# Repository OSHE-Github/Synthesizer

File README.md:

# Synthesizer

**Tips for uploading and running firmware on the Teensy**

- You will need the Arduino IDE to upload the firmware to the Teensy. Instructions: [Arduino IDE install instructions](https://support.arduino.cc/hc/en-us/articles/360019833020-Download-and-install-Arduino-IDE)
- Once Arduino IDE is installed, you will need the Teensyduino support package for Arduino IDE. Instructions: [Teensyduino install instructions](https://www.pjrc.com/teensy/td_download.html)
- You will also need to add the MIDI library into Arduino IDE. Instructions: [MIDI library instrall instructions](https://www.pjrc.com/teensy/td_libs_MIDI.html)
- The firmware should then be able to compile in Arduino IDE and upload to the Teensy by clicking the upload button. Make sure the Teensy is selected by going to Tools/Ports/ and select the correct serial port the Teensy is plugged into.

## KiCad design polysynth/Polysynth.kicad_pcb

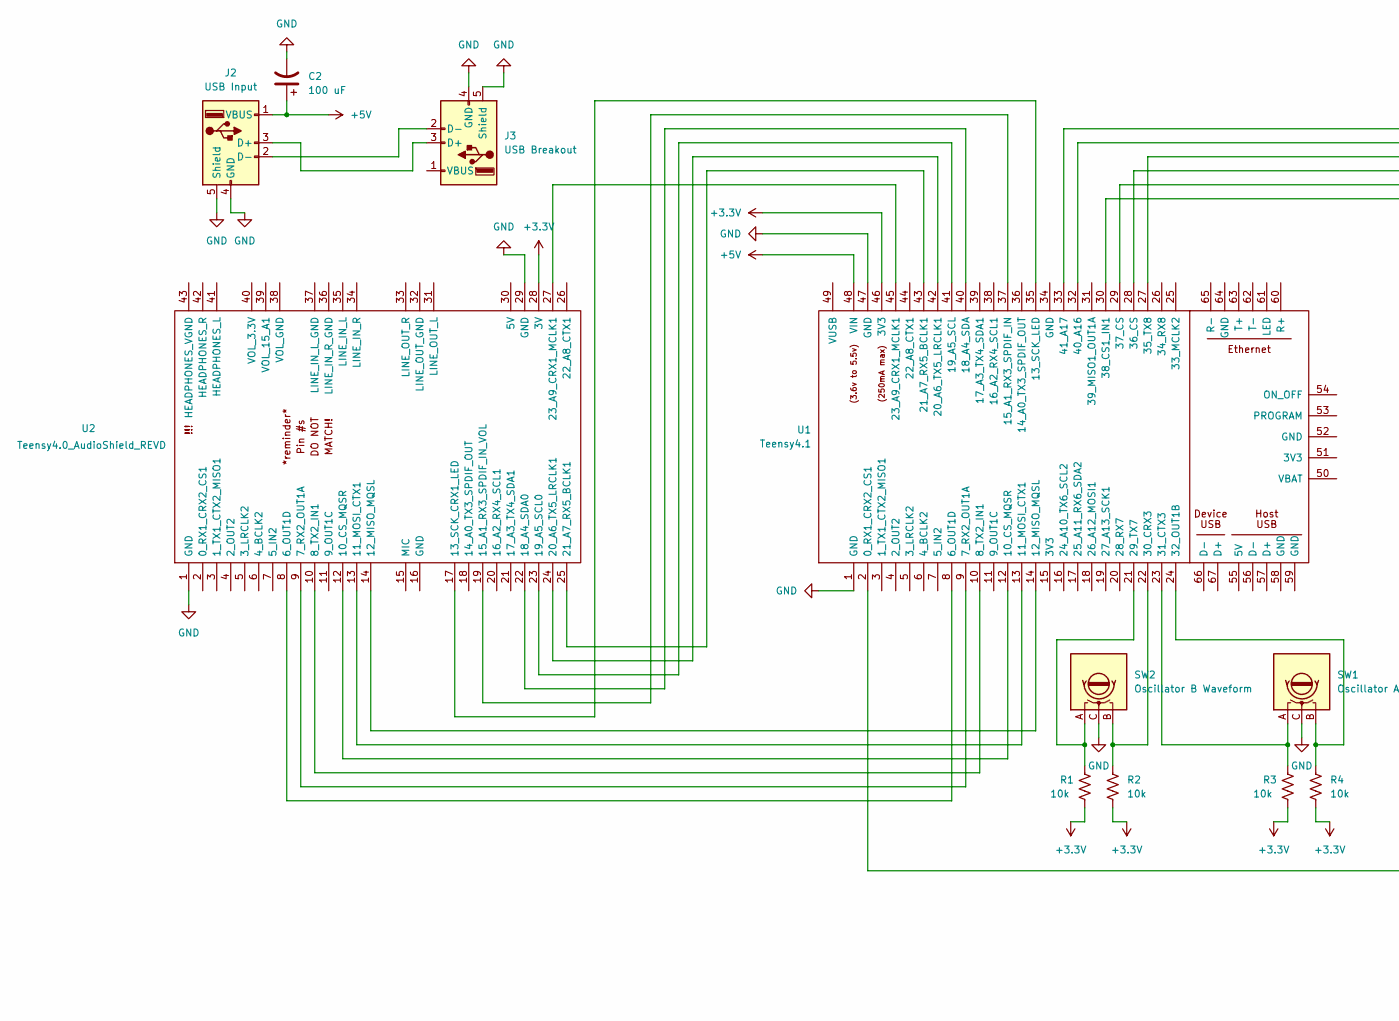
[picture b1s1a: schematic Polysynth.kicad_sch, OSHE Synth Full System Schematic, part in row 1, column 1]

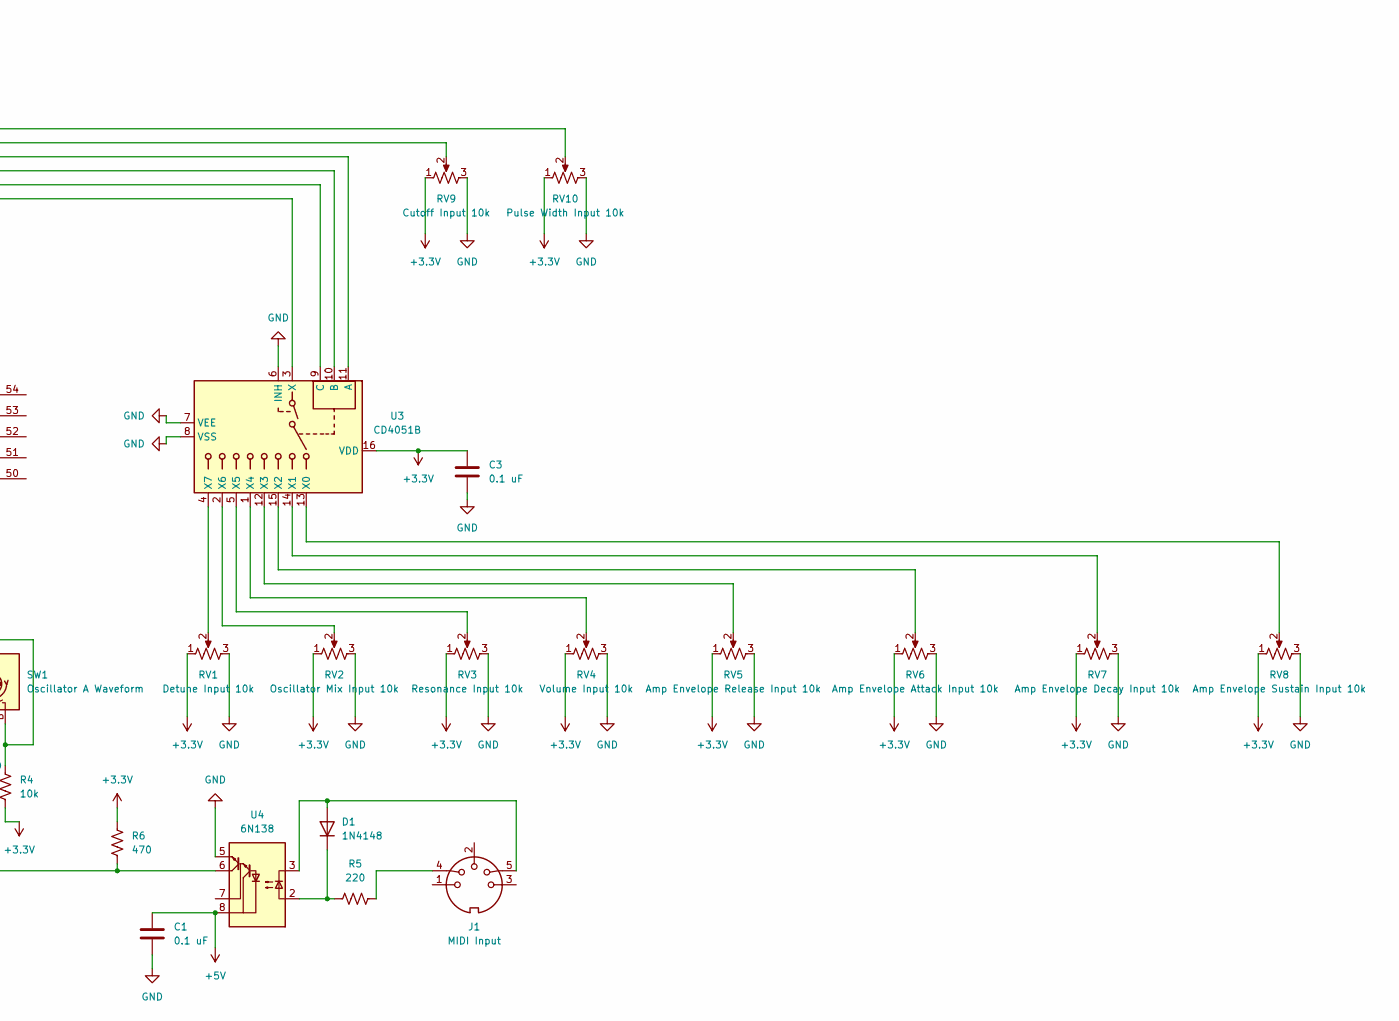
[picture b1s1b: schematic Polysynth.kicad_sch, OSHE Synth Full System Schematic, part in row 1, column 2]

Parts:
C1, C3: 0.1 uF; radial_cap
C2: 100 uF; radial_cap_med
D1: 1N4148; DO-35_02_VIS
J1: MIDI Input; MIDI
J2: USB Input; USB_A_Stewart_SS-52100-001_Horizontal
J3: USB Breakout; USB_A_Stewart_SS-52100-001_Horizontal
R1, R2, R3, R4: 10k; R_Axial_DIN0207_L6.3mm_D2.5mm_P10.16mm_Horizontal
R5: 220; R_Axial_DIN0207_L6.3mm_D2.5mm_P10.16mm_Horizontal
R6: 470; R_Axial_DIN0207_L6.3mm_D2.5mm_P10.16mm_Horizontal
RV1: Detune Input 10k; Potentiometer_Bourns_PTA4543_Single_Slide
RV2: Oscillator Mix Input 10k; PDB12H4301103BF
RV3: Resonance Input 10k; Potentiometer_Bourns_PTA4543_Single_Slide
RV4: Volume Input 10k; Potentiometer_Bourns_PTA4543_Single_Slide
RV5: Amp Envelope Release Input 10k; Potentiometer_Bourns_PTA4543_Single_Slide
RV6: Amp Envelope Attack Input 10k; Potentiometer_Bourns_PTA4543_Single_Slide
RV7: Amp Envelope Decay Input 10k; Potentiometer_Bourns_PTA4543_Single_Slide
RV8: Amp Envelope Sustain Input 10k; Potentiometer_Bourns_PTA4543_Single_Slide
RV9: Cutoff Input 10k; Potentiometer_Bourns_PTA4543_Single_Slide
RV10: Pulse Width Input 10k; Potentiometer_Bourns_PTA4543_Single_Slide
SW1: Oscillator A Waveform; RotaryEncoder_Bourns_Vertical_PEC12R-3x17F-Nxxxx
SW2: Oscillator B Waveform; RotaryEncoder_Bourns_Vertical_PEC12R-3x17F-Nxxxx
U1: Teensy4.1; Teensy41
U2: Teensy4.0_AudioShield_REVD; 4.0audioshield
U3: CD4051B; CD4051BE
U4: 6N138

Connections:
+3.3V: C3.1, R1.2, R2.2, R3.2, R4.2, R6.1, RV1.1, RV2.1, RV3.1, RV4.1, RV5.1, RV6.1, RV7.1, RV8.1, RV9.1, RV10.1, U1.46 (3V3), U2.28 (3V), U3.16 (VDD)
+5V: C1.2, C2.1, J2.1 (VBUS), U1.48 (VIN), U4.8 (VCC)
GND: C1.1, C2.2, C3.2, J2.4 (GND), J2.5 (Shield), J3.4 (GND), J3.5 (Shield), RV1.3, RV2.3, RV3.3, RV4.3, RV5.3, RV6.3, RV7.3, RV8.3, RV9.3, RV10.3, SW1.C, SW2.C, U1.1 (GND), U1.47 (GND), U2.1 (GND), U2.29 (GND), U3.6 (INH), U3.7 (VEE), U3.8 (VSS), U4.5 (GND)
unnamed: D1.2 (A), J1.5, U4.3 (C2)
unnamed: D1.1 (K), R5.1, U4.2 (C1)
unnamed: J1.4, R5.2
unnamed: J2.3 (D+), J3.3 (D+)
unnamed: J2.2 (D-), J3.2 (D-)
unnamed: R6.2, U1.2 (0_RX1_CRX2_CS1), U4.6 (VO2)
unnamed: U1.8 (6_OUT1D), U2.8 (6_OUT1D)
unnamed: U1.9 (7_RX2_OUT1A), U2.9 (7_RX2_OUT1A)
unnamed: U1.10 (8_TX2_IN1), U2.10 (8_TX2_IN1)
unnamed: U1.12 (10_CS_MQSR), U2.12 (10_CS_MQSR)
unnamed: U1.13 (11_MOSI_CTX1), U2.13 (11_MOSI_CTX1)
unnamed: U1.14 (12_MISO_MQSL), U2.14 (12_MISO_MQSL)
unnamed: U1.35 (13_SCK_LED), U2.17 (13_SCK_CRX1_LED)
unnamed: U1.37 (15_A1_RX3_SPDIF_IN), U2.19 (15_A1_RX3_SPDIF_IN_VOL)
unnamed: U1.40 (18_A4_SDA), U2.22 (18_A4_SDA0)
unnamed: U1.41 (19_A5_SCL), U2.23 (19_A5_SCL0)
unnamed: U1.42 (20_A6_TX5_LRCLK1), U2.24 (20_A6_TX5_LRCLK1)
unnamed: U1.43 (21_A7_RX5_BCLK1), U2.25 (21_A7_RX5_BCLK1)
unnamed: U1.45 (23_A9_CRX1_MCLK1), U2.27 (23_A9_CRX1_MCLK1)
unnamed: R1.1, SW2.A, U1.21 (29_TX7)
unnamed: R2.1, SW2.B, U1.22 (30_CRX3)
unnamed: R3.1, SW1.A, U1.23 (31_CTX3)
unnamed: R4.1, SW1.B, U1.24 (32_OUT1B)
unnamed: U1.27 (35_TX8), U3.11 (A)
unnamed: U1.28 (36_CS), U3.10 (B)
unnamed: U1.29 (37_CS), U3.9 (C)
unnamed: U1.30 (38_CS1_IN1), U3.3 (X)
unnamed: RV9.2, U1.32 (40_A16)
unnamed: RV10.2, U1.33 (41_A17)
unnamed: RV8.2, U3.13 (X0)
unnamed: RV7.2, U3.14 (X1)
unnamed: RV6.2, U3.15 (X2)
unnamed: RV5.2, U3.12 (X3)
unnamed: RV4.2, U3.1 (X4)
unnamed: RV3.2, U3.5 (X5)
unnamed: RV2.2, U3.2 (X6)
unnamed: RV1.2, U3.4 (X7)

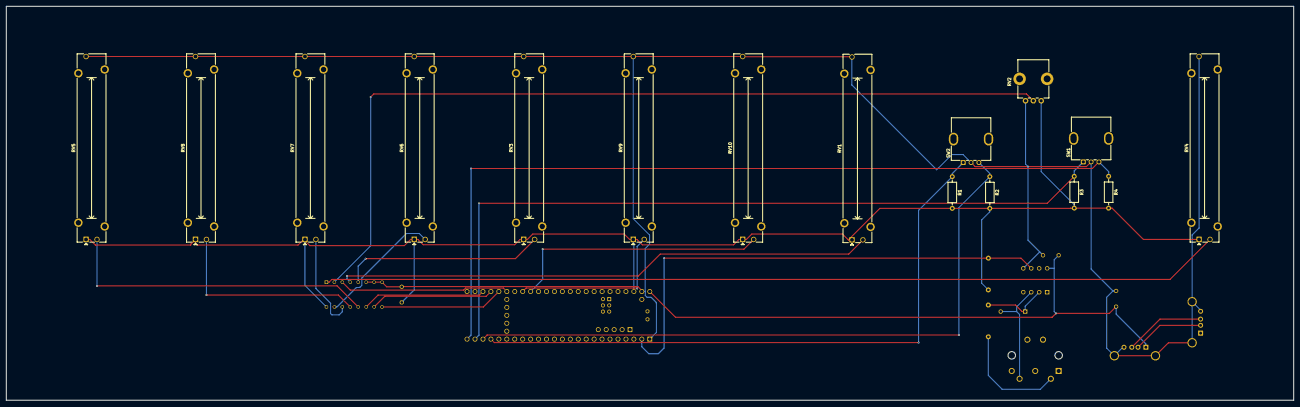
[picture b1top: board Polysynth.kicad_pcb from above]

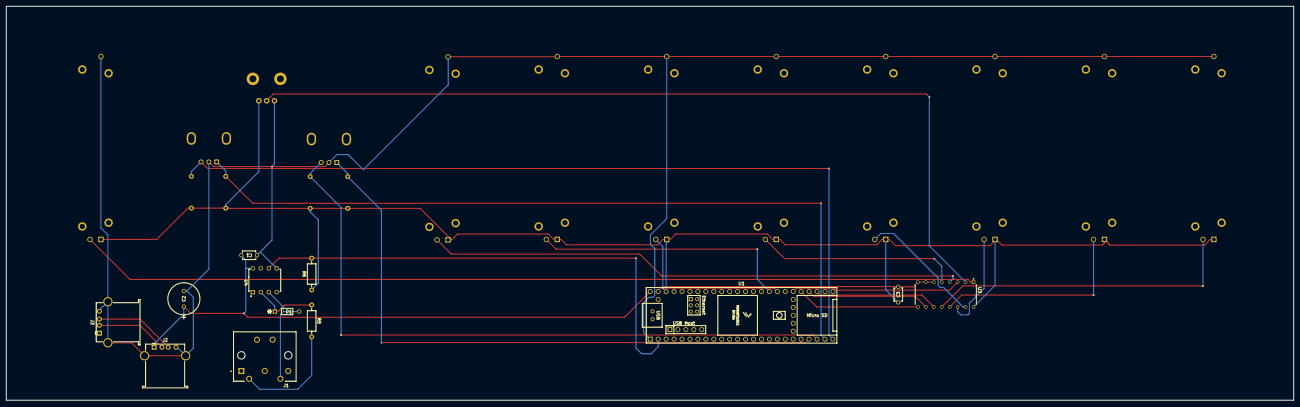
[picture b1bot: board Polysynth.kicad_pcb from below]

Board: 2 copper layers, 411.7 x 126.0 mm, 28 parts (12 on the bottom side), 27 nets.

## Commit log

2025-04-25 Adding all of these
